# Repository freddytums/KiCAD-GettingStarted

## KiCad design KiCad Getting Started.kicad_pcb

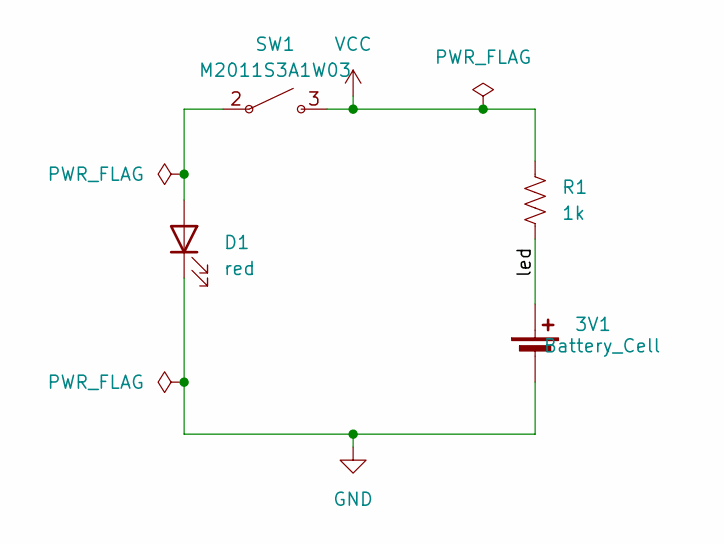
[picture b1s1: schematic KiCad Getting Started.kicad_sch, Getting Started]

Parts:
3V1: Battery_Cell; BatteryHolder_Keystone_1058_1x2032
D1: red; LED_D5.0mm
R1: 1k; R_Axial_DIN0309_L9.0mm_D3.2mm_P12.70mm_Horizontal
SW1: M2011S3A1W03; Switch_Toggle_SPST_NKK_M2011S3A1x03

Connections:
/led: 3V1.1 (+), R1.1
GND: 3V1.2 (-), D1.1 (K)
unnamed: D1.2 (A), SW1.2 (A)
VCC: R1.2, SW1.3 (B)

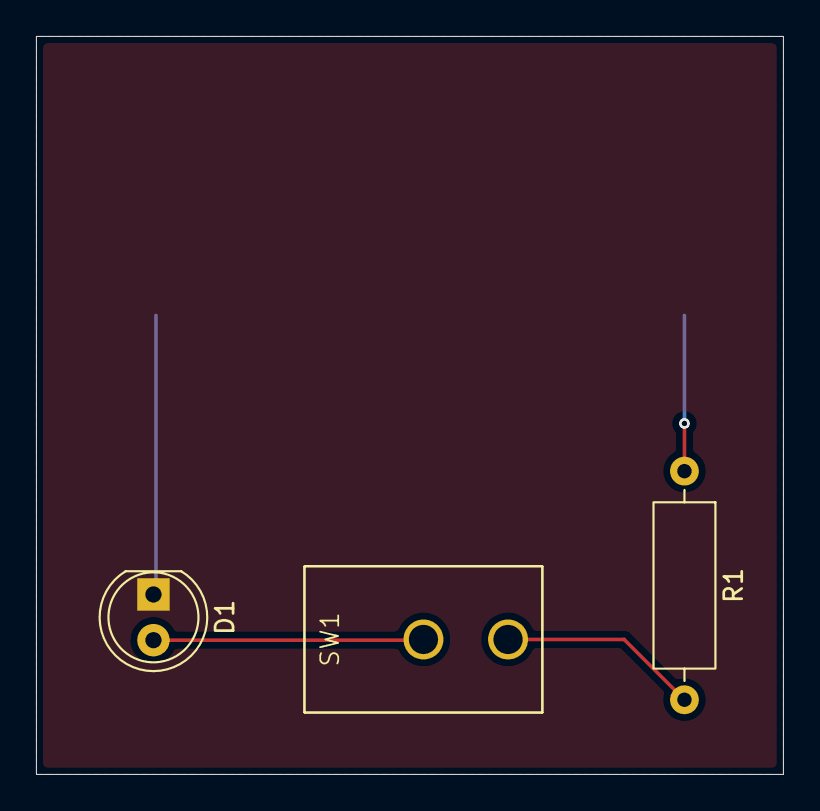
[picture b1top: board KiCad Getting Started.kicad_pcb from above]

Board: 2 copper layers, 41.5 x 41.0 mm, 4 parts (1 on the bottom side), 4 nets.

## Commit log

2026-05-30 Test Commit
2026-05-30 Test Commit 2
2026-05-30 Schematic Tutorial
2026-05-30 Schematic editing
2026-05-30 Made a Switch
2026-05-30 Done!
2026-05-30 Stop tracking .history snapshots
